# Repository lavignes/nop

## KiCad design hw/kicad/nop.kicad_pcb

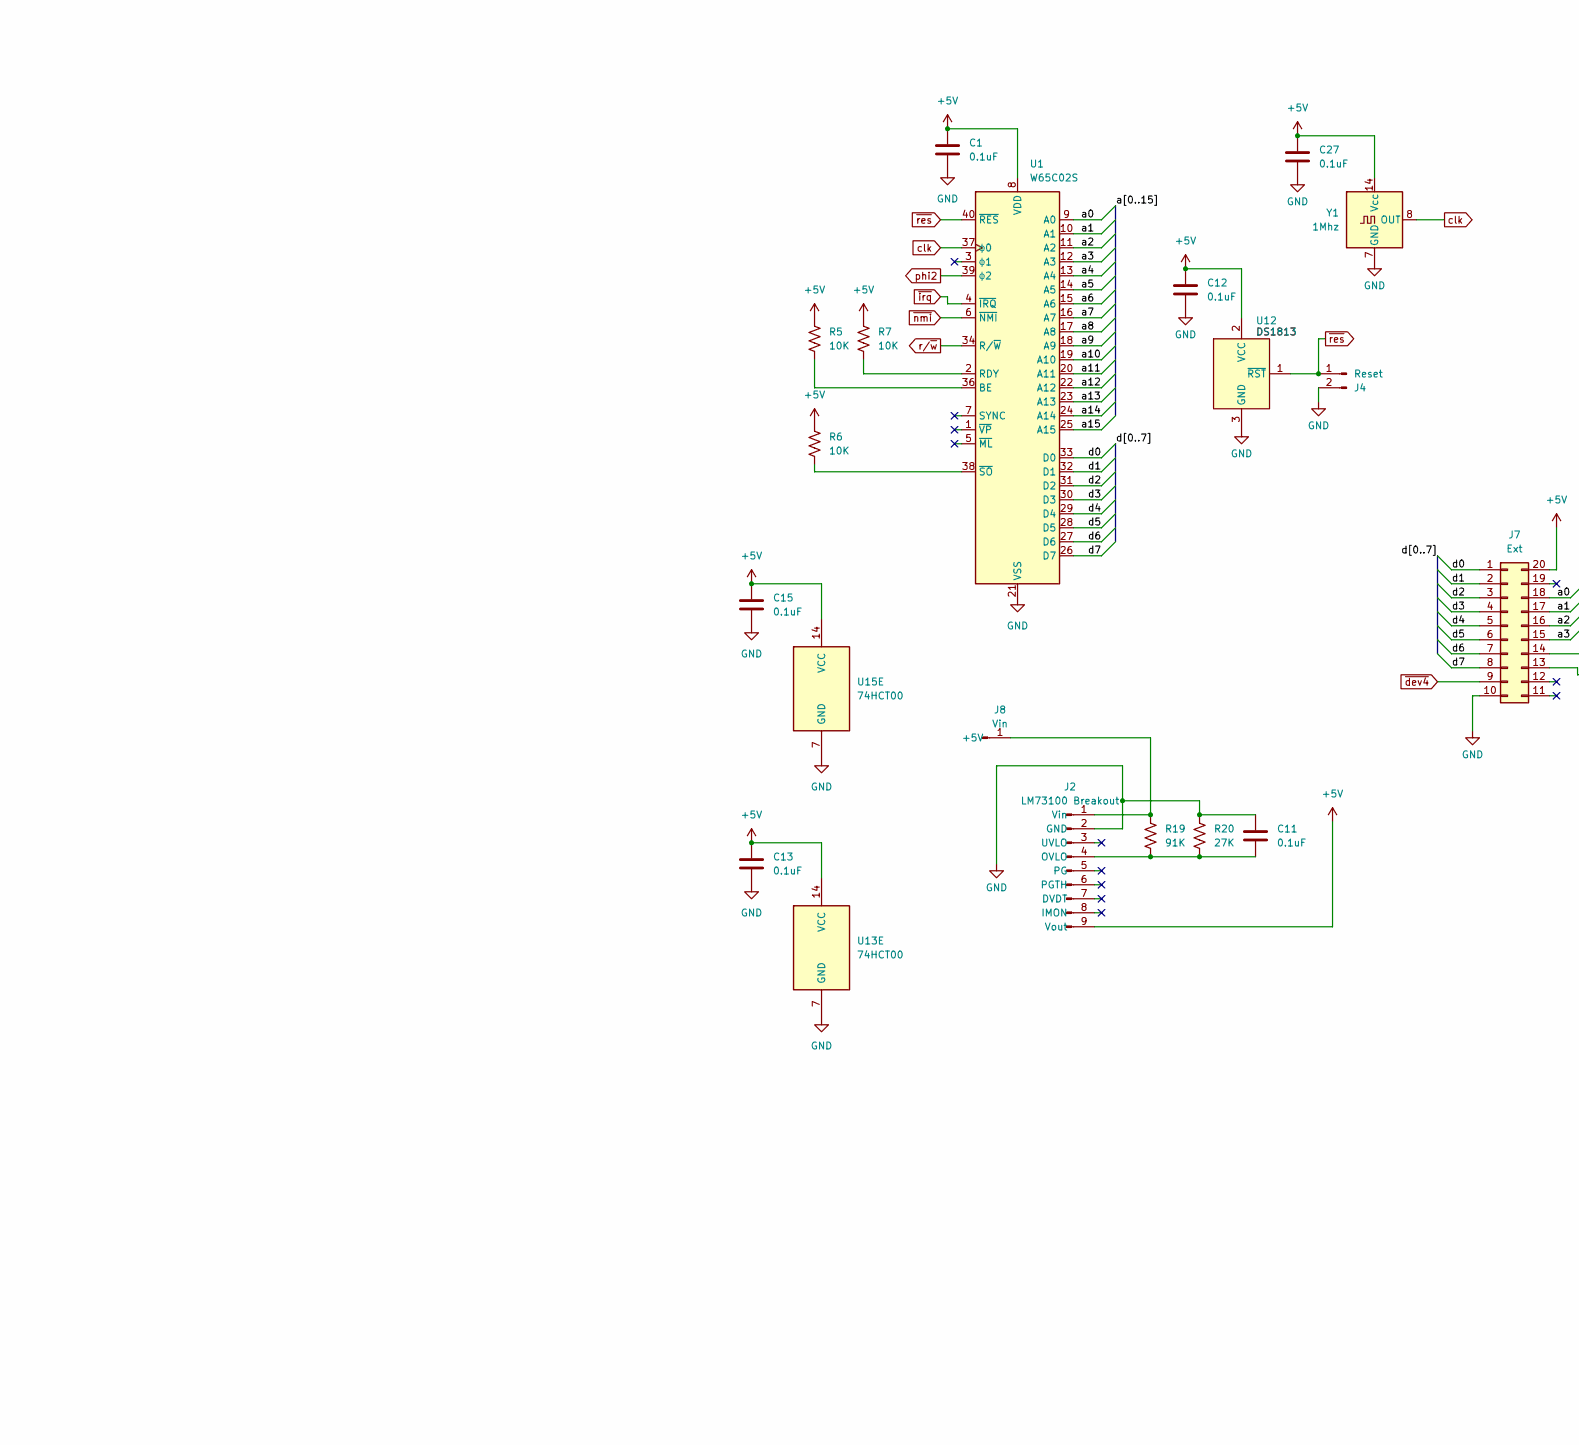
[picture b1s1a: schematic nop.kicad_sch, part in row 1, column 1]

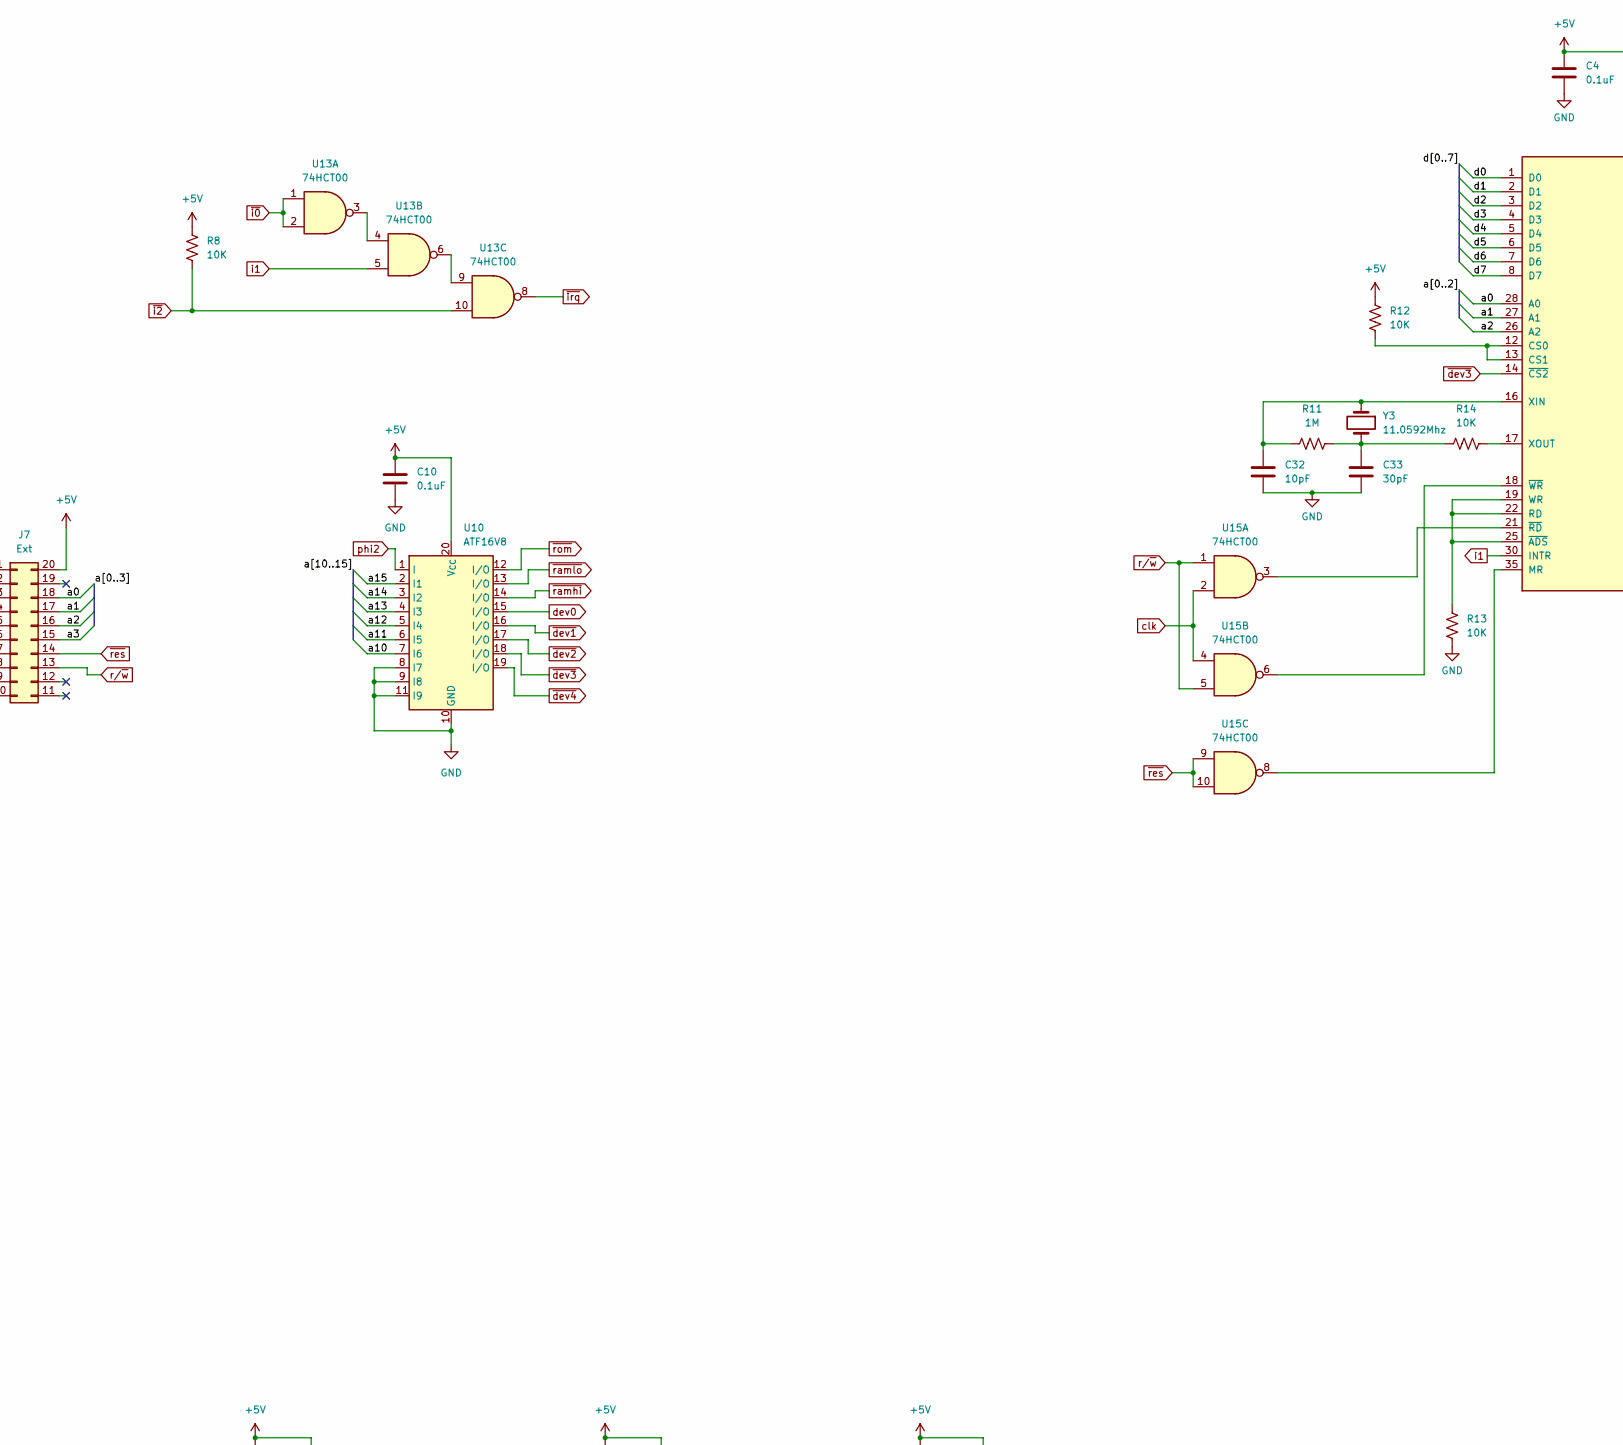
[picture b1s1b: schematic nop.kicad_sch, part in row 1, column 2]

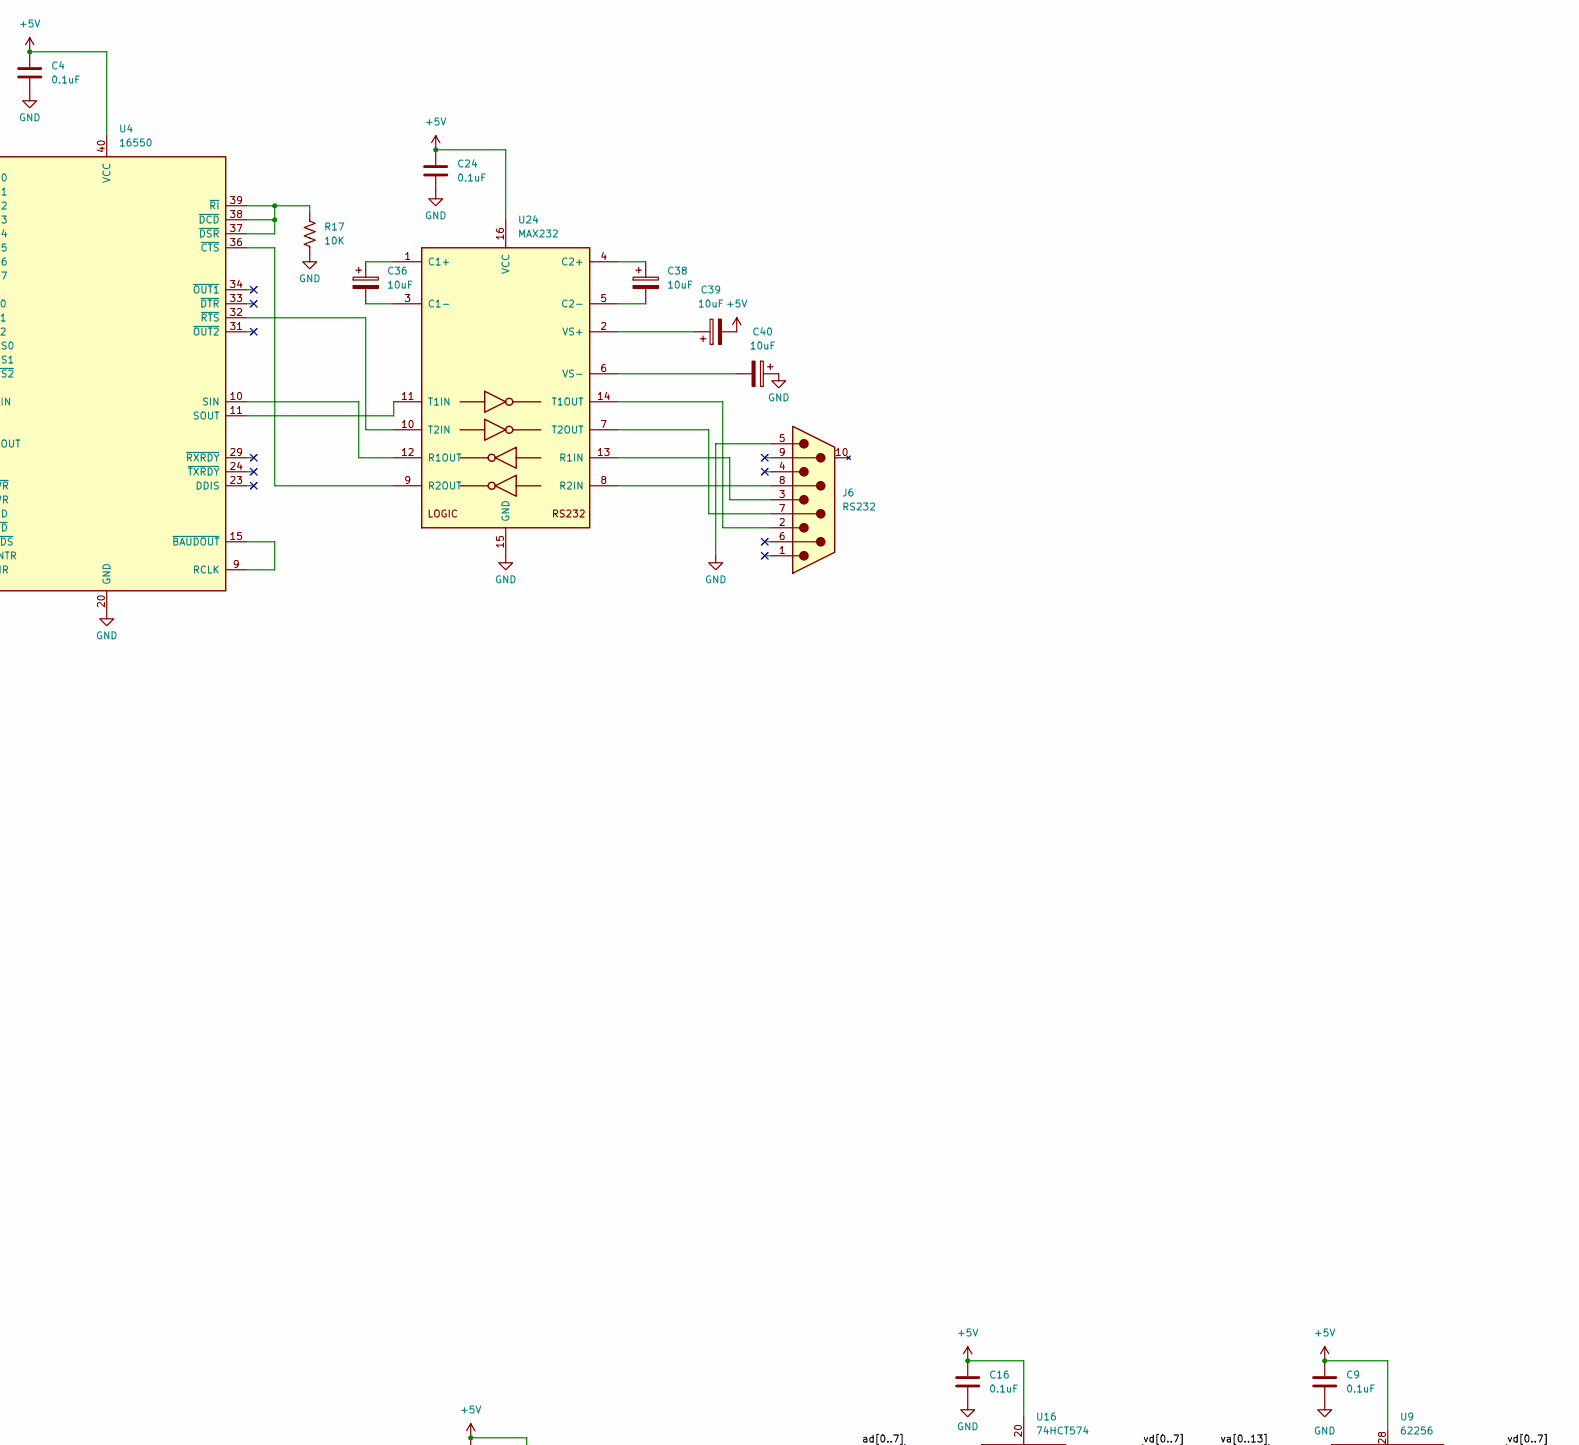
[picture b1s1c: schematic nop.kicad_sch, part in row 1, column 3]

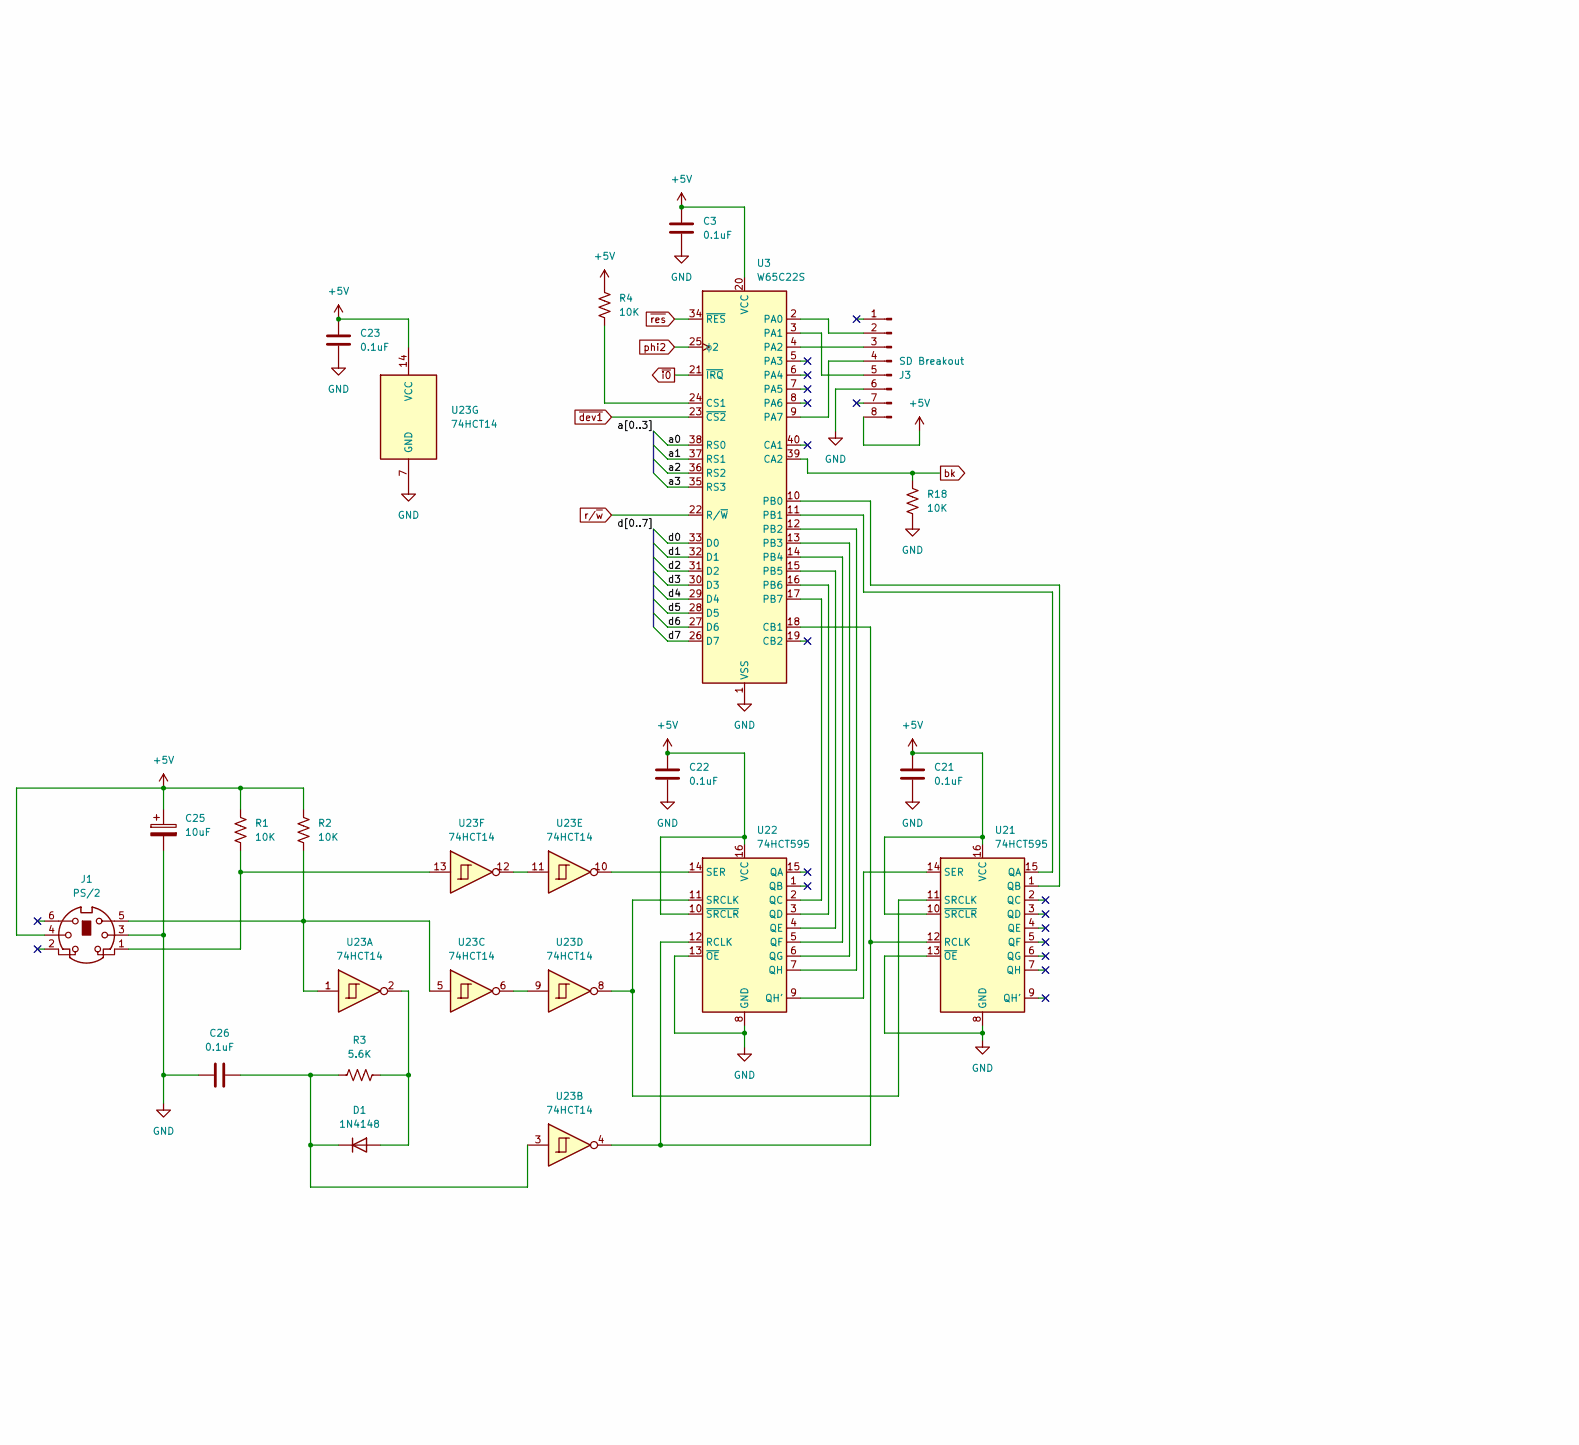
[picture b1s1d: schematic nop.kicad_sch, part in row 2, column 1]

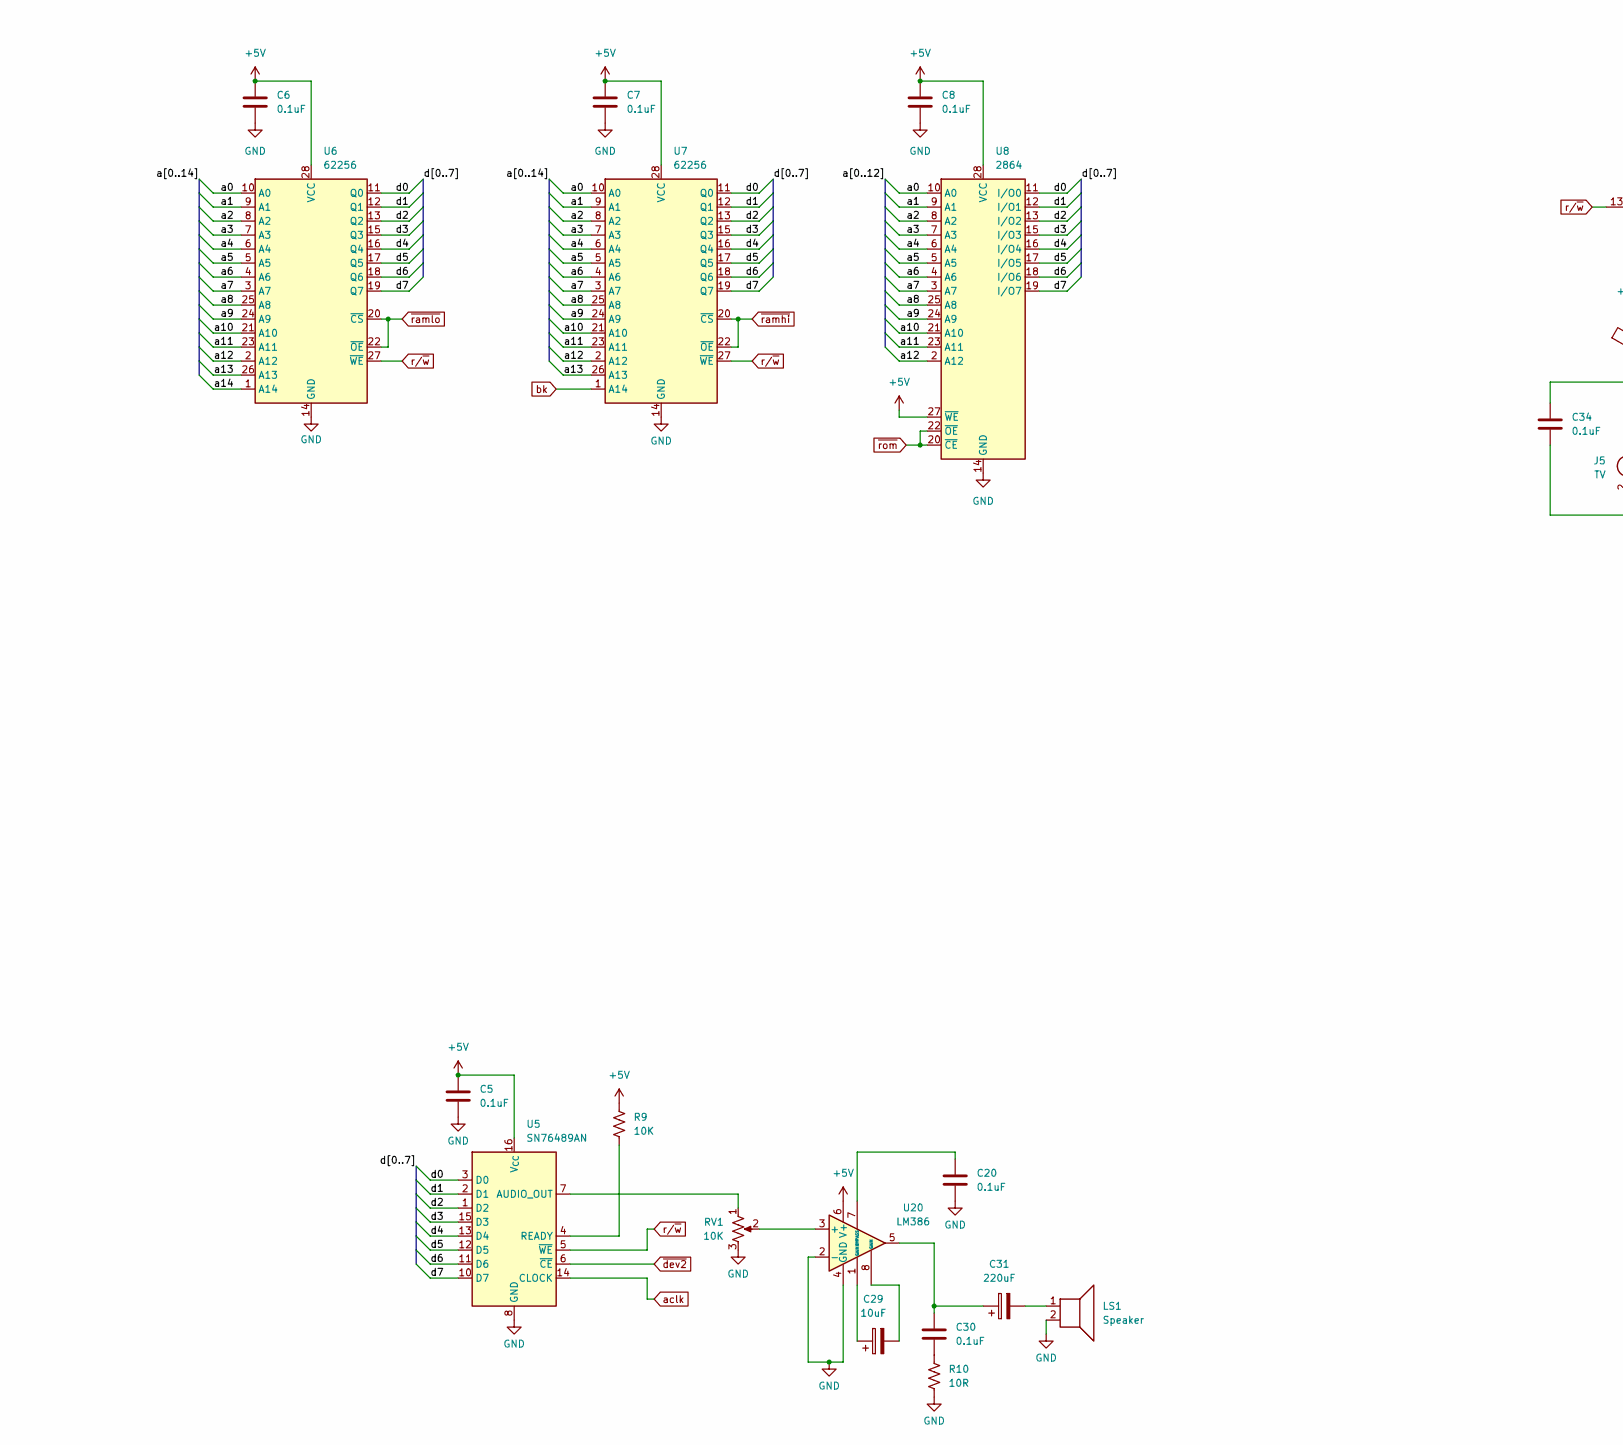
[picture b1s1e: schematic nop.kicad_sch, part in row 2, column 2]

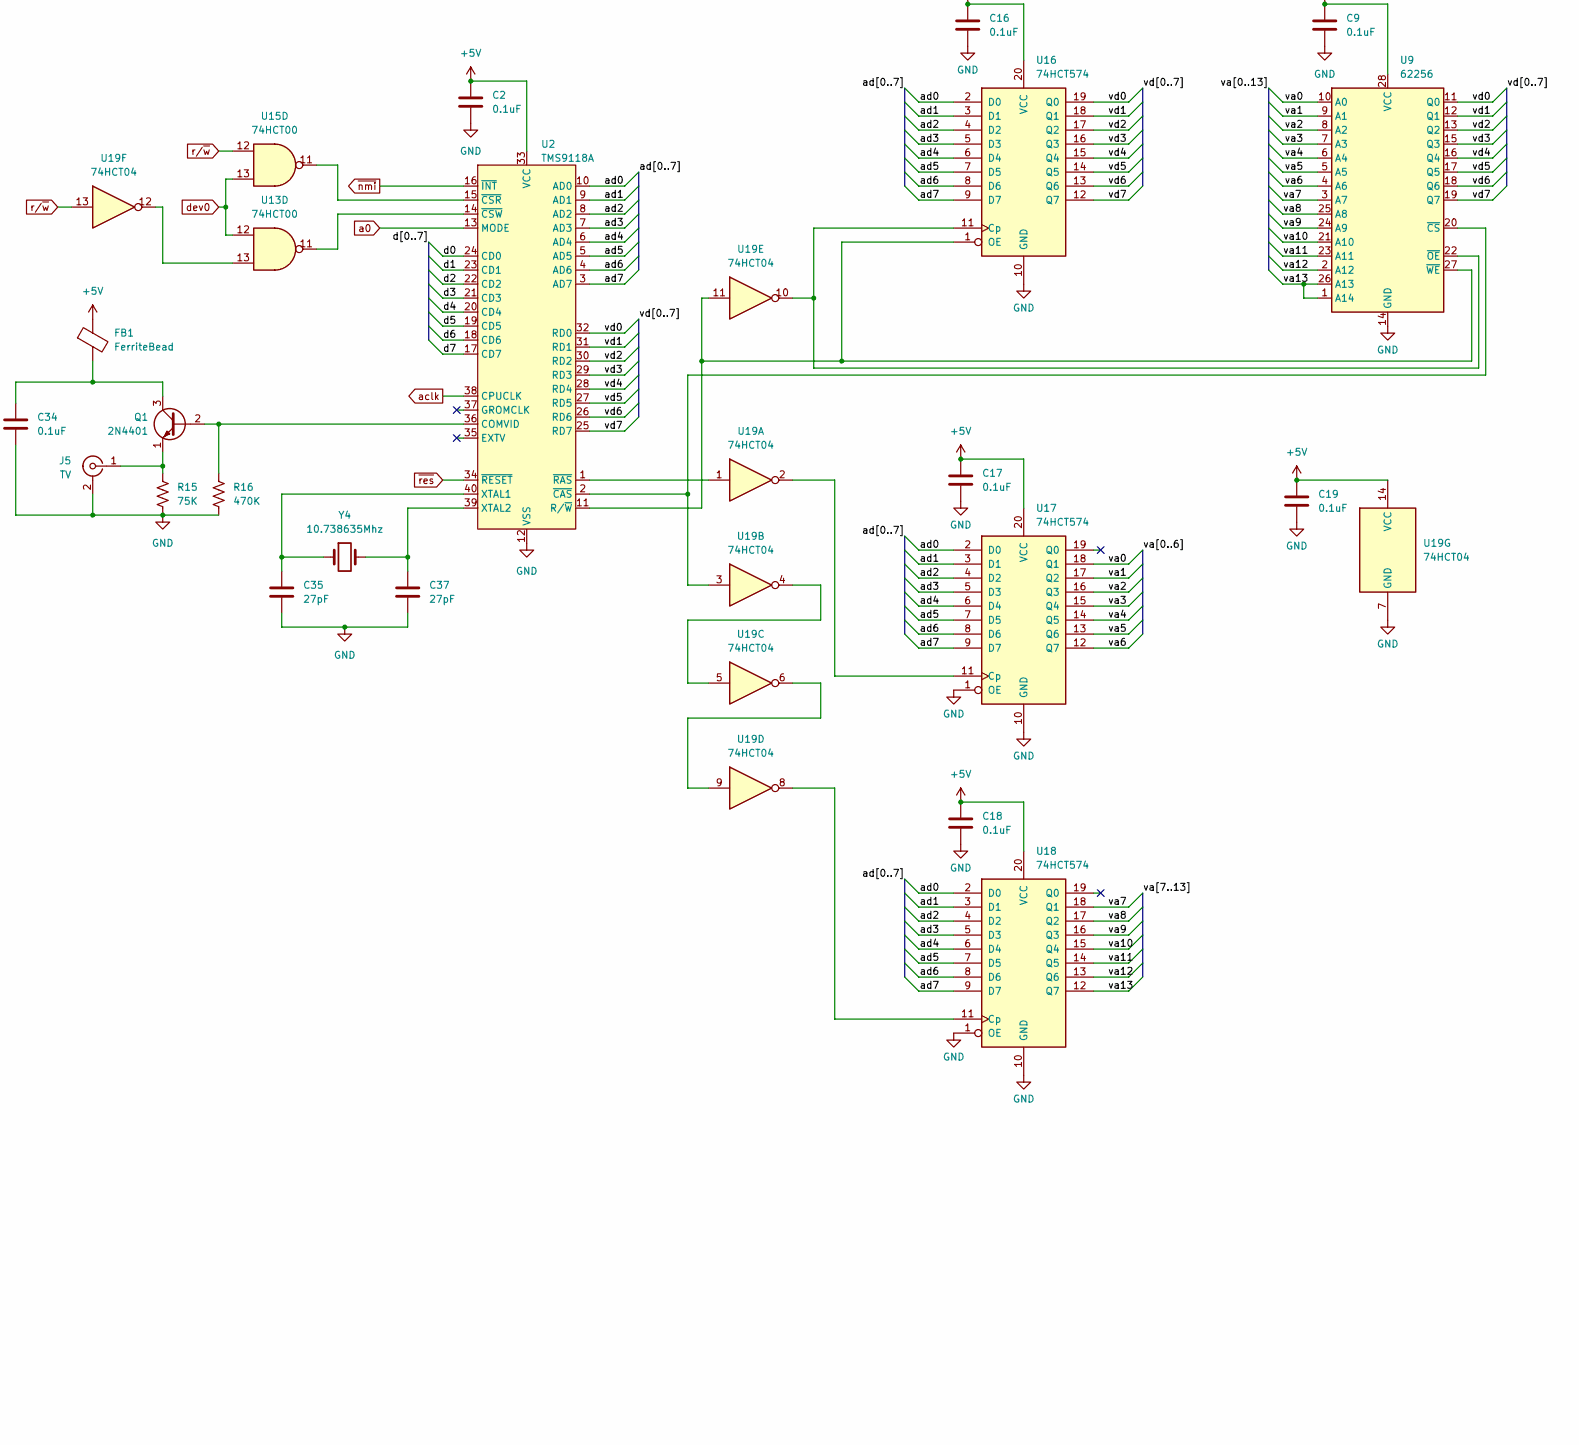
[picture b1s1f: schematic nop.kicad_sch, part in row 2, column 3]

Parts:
C1, C2, C3, C4, C5, C6, C7, C8, C9, C10, C11, C12, C13, C15, C16, C17, C18, C19, C20, C21, C22, C23, C24, C26, C27, C30, C34: 0.1uF; C_Disc_D7.5mm_W4.4mm_P5.00mm
C25, C29, C36, C38, C39, C40: 10uF; CP_Radial_D5.0mm_P2.50mm
C31: 220uF; CP_Radial_D5.0mm_P2.50mm
C32: 10pF; C_Disc_D7.5mm_W4.4mm_P5.00mm
C33: 30pF; C_Disc_D7.5mm_W4.4mm_P5.00mm
C35, C37: 27pF; C_Disc_D7.5mm_W4.4mm_P5.00mm
D1: 1N4148; D_DO-35_SOD27_P7.62mm_Horizontal
FB1: FerriteBead; L_Axial_L5.3mm_D2.2mm_P7.62mm_Horizontal_Vishay_IM-1
J1: PS/2; PinHeader_1x06_P2.54mm_Vertical
J2: LM73100 Breakout; PinHeader_1x09_P2.54mm_Vertical
J3: SD Breakout; PinHeader_1x08_P2.54mm_Vertical
J4: Reset; PinHeader_1x02_P2.54mm_Vertical
J5: TV; PinHeader_1x02_P2.54mm_Vertical
J6: RS232; PinHeader_2x05_P2.54mm_Vertical
J7: Ext; PinHeader_2x10_P2.54mm_Vertical
J8: Vin; PinHeader_1x01_P2.54mm_Vertical
LS1: Speaker; PinHeader_1x02_P2.54mm_Vertical
Q1: 2N4401; TO-92
R1, R2, R4, R5, R6, R7, R8, R9, R12, R13, R14, R17, R18: 10K; R_Axial_DIN0204_L3.6mm_D1.6mm_P7.62mm_Horizontal
R3: 5.6K; R_Axial_DIN0204_L3.6mm_D1.6mm_P7.62mm_Horizontal
R10: 10R; R_Axial_DIN0204_L3.6mm_D1.6mm_P7.62mm_Horizontal
R11: 1M; R_Axial_DIN0204_L3.6mm_D1.6mm_P7.62mm_Horizontal
R15: 75K; R_Axial_DIN0204_L3.6mm_D1.6mm_P7.62mm_Horizontal
R16: 470K; R_Axial_DIN0204_L3.6mm_D1.6mm_P7.62mm_Horizontal
R19: 91K; R_Axial_DIN0204_L3.6mm_D1.6mm_P7.62mm_Horizontal
R20: 27K; R_Axial_DIN0204_L3.6mm_D1.6mm_P7.62mm_Horizontal
RV1: 10K; PinHeader_1x03_P2.54mm_Vertical
U1: W65C02S; DIP-40_W15.24mm_Socket
U2: TMS9118A; DIP-40_W15.24mm_Socket
U3: W65C22S; DIP-40_W15.24mm_Socket
U4: 16550; DIP-40_W15.24mm_Socket
U5: SN76489AN; DIP-16_W7.62mm_Socket
U6, U7, U9: 62256; DIP-28_W15.24mm_Socket
U8: 2864; DIP-28_W15.24mm_Socket
U10: ATF16V8; DIP-20_W7.62mm_Socket
U12: DS1813; TO-92
U13, U15: 74HCT00; DIP-14_W7.62mm_Socket
U16, U17, U18: 74HCT574; DIP-20_W7.62mm_Socket
U19: 74HCT04; DIP-14_W7.62mm_Socket
U20: LM386; DIP-8_W7.62mm_Socket
U21, U22: 74HCT595; DIP-16_W7.62mm_Socket
U23: 74HCT14; DIP-14_W7.62mm_Socket
U24: MAX232; DIP-16_W7.62mm_Socket
Y1: 1Mhz; Oscillator_DIP-14
Y3: 11.0592Mhz; Crystal_HC49-4H_Vertical
Y4: 10.738635Mhz; Crystal_HC49-4H_Vertical

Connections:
+5V: C1.1, C2.1, C3.1, C4.1, C5.1, C6.1, C7.1, C8.1, C9.1, C10.1, C12.1, C13.1, C15.1, C16.1, C17.1, C18.1, C19.1, C21.1, C22.1, C23.1, C24.1, C25.1, C27.1, C39.2, FB1.1, J1.4, J2.9 (Vout), J3.8 (5v), J7.20, R1.2, R2.2, R4.2, R5.2, R6.2, R7.2, R8.2, R9.2, R12.2, U1.8 (VDD), U2.33 (VCC), U3.20 (VCC), U4.40 (VCC), U5.16 (V_{CC}), U6.28 (VCC), U7.28 (VCC), U8.27 (~WE), U8.28 (VCC), U9.28 (VCC), U10.20 (V_{CC}), U12.2 (VCC), U13.14 (VCC), U15.14 (VCC), U16.20 (VCC), U17.20 (VCC), U18.20 (VCC), U19.14 (VCC), U20.6 (V+), U21.10 (~SRCLR), U21.16 (VCC), U22.10 (~SRCLR), U22.16 (VCC), U23.14 (VCC), U24.16 (VCC), Y1.14 (Vcc)
/a1: J7.17, U1.10 (A1), U3.37 (RS1), U4.27 (A1), U6.9 (A1), U7.9 (A1), U8.9 (A1)
/a2: J7.16, U1.11 (A2), U3.36 (RS2), U4.26 (A2), U6.8 (A2), U7.8 (A2), U8.8 (A2)
/a3: J7.15, U1.12 (A3), U3.35 (RS3), U6.7 (A3), U7.7 (A3), U8.7 (A3)
/a4: U1.13 (A4), U6.6 (A4), U7.6 (A4), U8.6 (A4)
/a5: U1.14 (A5), U6.5 (A5), U7.5 (A5), U8.5 (A5)
/a6: U1.15 (A6), U6.4 (A6), U7.4 (A6), U8.4 (A6)
/a7: U1.16 (A7), U6.3 (A7), U7.3 (A7), U8.3 (A7)
/a8: U1.17 (A8), U6.25 (A8), U7.25 (A8), U8.25 (A8)
/a9: U1.18 (A9), U6.24 (A9), U7.24 (A9), U8.24 (A9)
/a10: U1.19 (A10), U6.21 (A10), U7.21 (A10), U8.21 (A10), U10.7 (I6)
/a11: U1.20 (A11), U6.23 (A11), U7.23 (A11), U8.23 (A11), U10.6 (I5)
/a12: U1.22 (A12), U6.2 (A12), U7.2 (A12), U8.2 (A12), U10.5 (I4)
/a13: U1.23 (A13), U6.26 (A13), U7.26 (A13), U10.4 (I3)
/a14: U1.24 (A14), U6.1 (A14), U10.3 (I2)
/a15: U1.25 (A15), U10.2 (I1)
/ad0: U2.10 (AD0), U16.2 (D0), U17.2 (D0), U18.2 (D0)
/ad1: U2.9 (AD1), U16.3 (D1), U17.3 (D1), U18.3 (D1)
/ad2: U2.8 (AD2), U16.4 (D2), U17.4 (D2), U18.4 (D2)
/ad3: U2.7 (AD3), U16.5 (D3), U17.5 (D3), U18.5 (D3)
/ad4: U2.6 (AD4), U16.6 (D4), U17.6 (D4), U18.6 (D4)
/ad5: U2.5 (AD5), U16.7 (D5), U17.7 (D5), U18.7 (D5)
/ad6: U2.4 (AD6), U16.8 (D6), U17.8 (D6), U18.8 (D6)
/ad7: U2.3 (AD7), U16.9 (D7), U17.9 (D7), U18.9 (D7)
/d0: J7.1, U1.33 (D0), U2.24 (CD0), U3.33 (D0), U4.1 (D0), U5.3 (D0), U6.11 (Q0), U7.11 (Q0), U8.11 (I/O0)
/d1: J7.2, U1.32 (D1), U2.23 (CD1), U3.32 (D1), U4.2 (D1), U5.2 (D1), U6.12 (Q1), U7.12 (Q1), U8.12 (I/O1)
/d2: J7.3, U1.31 (D2), U2.22 (CD2), U3.31 (D2), U4.3 (D2), U5.1 (D2), U6.13 (Q2), U7.13 (Q2), U8.13 (I/O2)
/d3: J7.4, U1.30 (D3), U2.21 (CD3), U3.30 (D3), U4.4 (D3), U5.15 (D3), U6.15 (Q3), U7.15 (Q3), U8.15 (I/O3)
/d4: J7.5, U1.29 (D4), U2.20 (CD4), U3.29 (D4), U4.5 (D4), U5.13 (D4), U6.16 (Q4), U7.16 (Q4), U8.16 (I/O4)
/d5: J7.6, U1.28 (D5), U2.19 (CD5), U3.28 (D5), U4.6 (D5), U5.12 (D5), U6.17 (Q5), U7.17 (Q5), U8.17 (I/O5)
/d6: J7.7, U1.27 (D6), U2.18 (CD6), U3.27 (D6), U4.7 (D6), U5.11 (D6), U6.18 (Q6), U7.18 (Q6), U8.18 (I/O6)
/d7: J7.8, U1.26 (D7), U2.17 (CD7), U3.26 (D7), U4.8 (D7), U5.10 (D7), U6.19 (Q7), U7.19 (Q7), U8.19 (I/O7)
/va0: U9.10 (A0), U17.18 (Q1)
/va1: U9.9 (A1), U17.17 (Q2)
/va2: U9.8 (A2), U17.16 (Q3)
/va3: U9.7 (A3), U17.15 (Q4)
/va4: U9.6 (A4), U17.14 (Q5)
/va5: U9.5 (A5), U17.13 (Q6)
/va6: U9.4 (A6), U17.12 (Q7)
/va7: U9.3 (A7), U18.18 (Q1)
/va8: U9.25 (A8), U18.17 (Q2)
/va9: U9.24 (A9), U18.16 (Q3)
/va10: U9.21 (A10), U18.15 (Q4)
/va11: U9.23 (A11), U18.14 (Q5)
/va12: U9.2 (A12), U18.13 (Q6)
/va13: U9.1 (A14), U9.26 (A13), U18.12 (Q7)
/vd0: U2.32 (RD0), U9.11 (Q0), U16.19 (Q0)
/vd1: U2.31 (RD1), U9.12 (Q1), U16.18 (Q1)
/vd2: U2.30 (RD2), U9.13 (Q2), U16.17 (Q2)
/vd3: U2.29 (RD3), U9.15 (Q3), U16.16 (Q3)
/vd4: U2.28 (RD4), U9.16 (Q4), U16.15 (Q4)
/vd5: U2.27 (RD5), U9.17 (Q5), U16.14 (Q5)
/vd6: U2.26 (RD6), U9.18 (Q6), U16.13 (Q6)
/vd7: U2.25 (RD7), U9.19 (Q7), U16.12 (Q7)
GND: C1.2, C2.2, C3.2, C4.2, C5.2, C6.2, C7.2, C8.2, C9.2, C10.2, C11.1, C12.2, C13.2, C15.2, C16.2, C17.2, C18.2, C19.2, C20.2, C21.2, C22.2, C23.2, C24.2, C25.2, C26.1, C27.2, C32.2, C33.2, C34.2, C35.2, C37.2, C40.1, J1.3, J2.2 (GND), J3.6 (GND), J4.2, J5.2 (Ext), J6.5, J7.10, LS1.2, R10.1, R13.1, R15.1, R16.1, R17.1, R18.1, R20.2, RV1.3, U1.21 (VSS), U2.12 (VSS), U3.1 (VSS), U4.20 (GND), U5.8 (GND), U6.14 (GND), U7.14 (GND), U8.14 (GND), U9.14 (GND), U10.8 (I7), U10.9 (I8), U10.10 (GND), U10.11 (I9), U12.3 (GND), U13.7 (GND), U15.7 (GND), U16.10 (GND), U17.1 (OE), U17.10 (GND), U18.1 (OE), U18.10 (GND), U19.7 (GND), U20.2 (-), U20.4 (GND), U21.8 (GND), U21.13 (~OE), U22.8 (GND), U22.13 (~OE), U23.7 (GND), U24.15 (GND), Y1.7 (GND)
unnamed: C29.1, U20.1 (GAIN)
unnamed: C29.2, U20.8 (GAIN)
unnamed: C30.1, C31.1, U20.5
unnamed: C30.2, R10.2
unnamed: C31.2, LS1.1
unnamed: C33.1, R11.1, R14.2, Y3.2
unnamed: D1.2 (A), R3.1, U23.2
unnamed: C26.2, D1.1 (K), R3.2, U23.3
unnamed: J1.1, R1.1, U23.13
unnamed: J1.5, R2.1, U23.1, U23.5
unnamed: C11.2, J2.4 (OVLO), R19.1, R20.1
unnamed: J2.1 (Vin), J8.1, R19.2
unnamed: J3.5 (CLK), U3.3 (PA1)
unnamed: J3.2 (CS), U3.2 (PA0)
unnamed: J3.3 (DI), U3.4 (PA2)
unnamed: J3.4 (DO), U3.9 (PA7)
unnamed: J5.1 (In), Q1.1 (E), R15.2
unnamed: Q1.2 (B), R16.2, U2.36 (COMVID)
unnamed: C34.1, FB1.2, Q1.3 (C)
unnamed: R5.1, U1.36 (BE)
unnamed: R7.1, U1.2 (RDY)
unnamed: R6.1, U1.38 (~SO)
unnamed: C35.1, U2.40 (XTAL1), Y4.1
unnamed: C37.1, U2.39 (XTAL2), Y4.2
unnamed: U2.2 (~CAS), U9.20 (~CS), U19.3
unnamed: U2.15 (~CSR), U15.11
unnamed: U2.14 (~CSW), U13.11
unnamed: U2.1 (~RAS), U19.1
unnamed: R4.1, U3.24 (CS1)
unnamed: R12.1, U4.12 (CS0), U4.13 (CS1)
unnamed: U4.35 (MR), U15.8
unnamed: U4.9 (RCLK), U4.15 (~BAUDOUT)
unnamed: R13.2, U4.19 (WR), U4.22 (RD), U4.25 (~ADS)
unnamed: C32.1, R11.2, U4.16 (XIN), Y3.1
unnamed: R14.1, U4.17 (XOUT)
unnamed: R17.2, U4.37 (~DSR), U4.38 (~DCD), U4.39 (~RI)
unnamed: U4.21 (~RD), U15.3
unnamed: U4.18 (~WR), U15.6
unnamed: RV1.1, U5.7 (AUDIO_OUT)
unnamed: R9.1, U5.4 (READY)
unnamed: U13.3, U13.4
unnamed: U13.6, U13.9
unnamed: U13.13, U19.12
unnamed: U9.22 (~OE), U16.11 (Cp), U19.10
unnamed: U2.11 (R/~W), U9.27 (~WE), U16.1 (OE), U19.11
unnamed: U17.11 (Cp), U19.2
unnamed: U18.11 (Cp), U19.8
unnamed: U19.4, U19.5
unnamed: U19.6, U19.9
unnamed: RV1.2, U20.3 (+)
unnamed: C20.1, U20.7 (BYPASS)
unnamed: U3.11 (PB1), U21.15 (QA)
unnamed: U3.10 (PB0), U21.1 (QB)
unnamed: U3.18 (CB1), U21.12 (RCLK), U22.12 (RCLK), U23.4
unnamed: U21.14 (SER), U22.9 (QH')
unnamed: U21.11 (SRCLK), U22.11 (SRCLK), U23.8
unnamed: U3.17 (PB7), U22.2 (QC)
unnamed: U3.16 (PB6), U22.3 (QD)
unnamed: U3.15 (PB5), U22.4 (QE)
unnamed: U3.14 (PB4), U22.5 (QF)
unnamed: U3.13 (PB3), U22.6 (QG)
unnamed: U3.12 (PB2), U22.7 (QH)
unnamed: U22.14 (SER), U23.10
unnamed: U23.6, U23.9
unnamed: U23.11, U23.12
unnamed: C36.1, U24.1 (C1+)
unnamed: C36.2, U24.3 (C1-)
unnamed: C38.1, U24.4 (C2+)
unnamed: C38.2, U24.5 (C2-)
unnamed: J6.3, U24.13 (R1IN)
unnamed: U4.10 (SIN), U24.12 (R1OUT)
unnamed: J6.8, U24.8 (R2IN)
unnamed: U4.36 (~CTS), U24.9 (R2OUT)
unnamed: U4.11 (SOUT), U24.11 (T1IN)
unnamed: J6.2, U24.14 (T1OUT)
unnamed: U4.32 (~RTS), U24.10 (T2IN)
unnamed: J6.7, U24.7 (T2OUT)
unnamed: C39.1, U24.2 (VS+)
unnamed: C40.2, U24.6 (VS-)
a0: J7.18, U1.9 (A0), U2.13 (MODE), U3.38 (RS0), U4.28 (A0), U6.10 (A0), U7.10 (A0), U8.10 (A0)
aclk: U2.38 (CPUCLK), U5.14 (CLOCK)
bk: R18.2, U3.39 (CA2), U7.1 (A14)
clk: U1.37 (ϕ0), U15.2, U15.4, Y1.8 (OUT)
dev0: U10.15 (I/O), U13.12, U15.13
i1: U4.30 (INTR), U13.5
phi2: U1.39 (ϕ2), U3.25 (ϕ2), U10.1 (I)
r/~w: J7.13, U1.34 (R/~W), U3.22 (R/~W), U5.5 (~WE), U6.27 (~WE), U7.27 (~WE), U15.1, U15.5, U15.12, U19.13
~dev1: U3.23 (~CS2), U10.16 (I/O)
~dev2: U5.6 (~CE), U10.17 (I/O)
~dev3: U4.14 (~CS2), U10.18 (I/O)
~dev4: J7.9, U10.19 (I/O)
~i0: U3.21 (~IRQ), U13.1, U13.2
~i2: R8.1, U13.10
~irq: U1.4 (~IRQ), U13.8
~nmi: U1.6 (~NMI), U2.16 (~INT)
~ramhi: U7.20 (~CS), U7.22 (~OE), U10.14 (I/O)
~ramlo: U6.20 (~CS), U6.22 (~OE), U10.13 (I/O)
~res: J4.1, J7.14, U1.40 (~RES), U2.34 (~RESET), U3.34 (~RES), U12.1 (~RST), U15.9, U15.10
~rom: U8.20 (~CE), U8.22 (~OE), U10.12 (I/O)

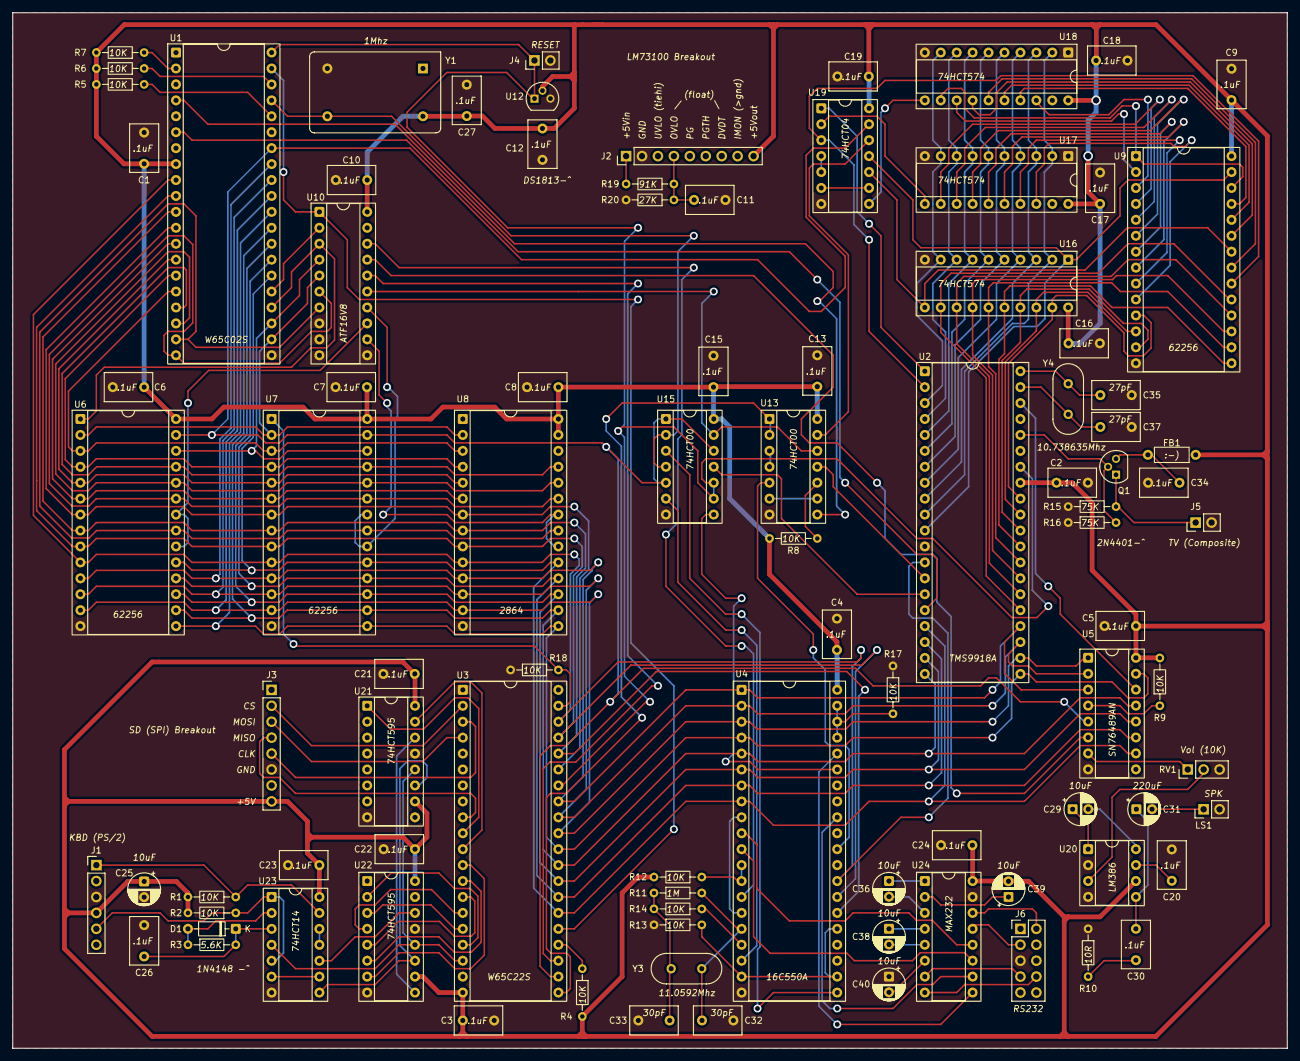
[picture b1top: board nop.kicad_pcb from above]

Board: 2 copper layers, 203.2 x 165.1 mm, 94 parts (0 on the bottom side), 153 nets.

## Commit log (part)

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2025-01-30 parse number base prefixes
2025-02-07 Add underscore support to literal parser
2025-02-09 good lookin ;)
2025-02-09 inlining
2025-02-10 interrupts be interruptin'
2025-02-10 we bootin
2025-02-10 add panic handler for undefined functions
2025-02-10 somethin
2025-02-10 fix insane repe bugs
2025-02-10 inline: still wonky
2025-02-10 Compile function length
2025-02-11 implement [lit]
2025-02-11 increase stack size
2025-06-17 fix messy linkerscript
2025-06-19 startin
2025-06-22 moar
2025-06-25 Split words ending in "
2025-06-30 more nop
2025-09-10 renames
2025-09-25 BufView -> View
2025-09-26 the num-ining
2025-09-28 most tokens
2025-09-29 keywords and constants
2025-09-30 reorganizing
2025-10-03 add tst ability
2025-10-03 unit test
2025-10-06 UNKNOWN type for first pass
2025-10-07 clean
2025-12-22 simplification...
    but the heap is still getting corrupted. Presumably during execution of
    `#b,` within the execution of `:Def`. Need to create some checkpoint
    words for debug purposes I think. Or just insert _Panics and inspect the
    state.
2025-12-22 optimize
    but its still borked
2025-12-25 x86 -> x86-pc-bios
2025-12-26 fix the bugs D:
2025-12-26 Compute code len
2025-12-28 move to 6502
2025-12-28 vm: fix ab* addressing modes
2025-12-28 vm: table-driven dis
2025-12-28 vm: table-driven doop
2025-12-28 vm: clean up code more
2025-12-28 vm: refactor debugger
2025-12-28 vm: shortest match debug cmd
2025-12-29 vmsys: working on interpreter
2025-12-29 vm: debug on illegal opcodes
2025-12-29 vm: make dis and exa commands take a length
2025-12-30 sys.s: add @b with sign-extend
2025-12-30 vm: fix @b
2025-12-30 vm: add next debug command
2025-12-30 vm: add libedit
2025-12-30 vm: bit of auto-complete cleanup
2026-01-03 checkpoint
2026-01-05 vm: add symbols to debugger
    it just makes it a little nicer and its not a lot of code
2026-01-05 vm: autocomplete anything
2026-01-05 vm: clean up some fluff
2026-01-07 vmsys: SysFind working
2026-01-07 vmsys: implement compile
2026-01-08 vmsys: add INEND sysvar
2026-01-08 vm: add subroutine labels to disasm
2026-01-09 vm: prepare for expression parser
2026-01-09 vm: add tok
2026-01-10 vm: expr parser
2026-01-10 fix parsing bug
2026-01-11 code is running
2026-01-11 vmsys: reduce code
2026-01-12 vm: fix sym name matching in expressions
2026-01-12 sysvm: start migration to lang-based code
2026-01-13 i dunno
2026-01-13 vmsys: bugs
2026-01-13 16bit scratch
2026-01-14 vm: add non-blocking io status and tx/rx register
2026-01-15 vmsys: drivers
2026-01-16 sysvm: Fix branch bug
2026-01-19 sysvm: inner interpreter working
2026-01-19 vmsys: _Load being funky
2026-01-20 sysvm: fix load, work on outer interp
2026-01-20 sysvm: fix read echo
2026-01-20 vm: \r\n for raw mode
2026-03-21 vm: save unique history items
